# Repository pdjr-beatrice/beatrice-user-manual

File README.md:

# beatrice-user-manual

This Docbook 5 project implements a user manual for the motor vessel "Beatrice of Hull".

The src/ directory contains the XML source in Docbook 5 "book" format.

The pub/ directory contains renderings of the user manual in various formats. The latest PDF rendering is available
<a href="pub/pdf/beatrice.pdf" download="beatrice">here</a>.

The status of this work is DRAFT.

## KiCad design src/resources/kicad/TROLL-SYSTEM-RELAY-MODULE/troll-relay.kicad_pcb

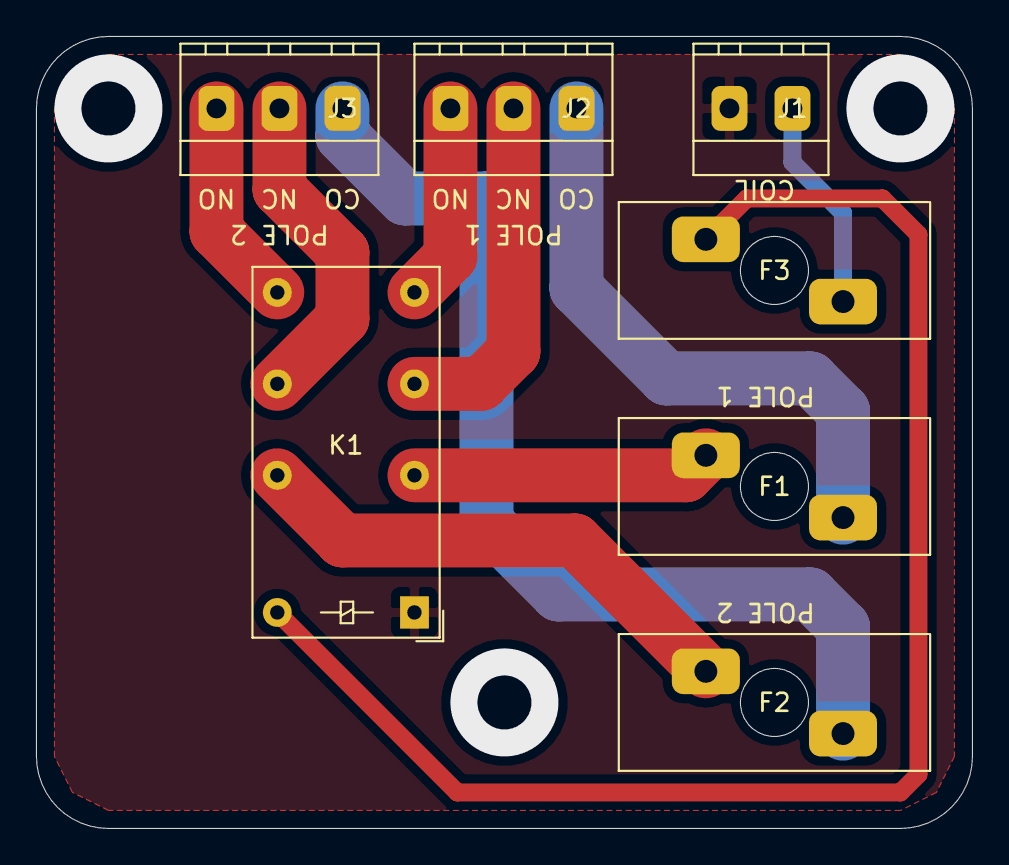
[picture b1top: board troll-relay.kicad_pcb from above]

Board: 2 copper layers, 52.0 x 44.0 mm, 7 parts (0 on the bottom side), 11 nets.

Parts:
F1, F2, F3: Fuse; LITTLEFUSE_153008
J1: Screw_Terminal_01x02; PHOENIX_MKDS_3.5MM_2-POLE_#1751248
J2, J3: Screw_Terminal_01x03; PHOENIX_MKDS_3.5MM_3-POLE_#1751251
K1: FINDER-30.22; Relay_DPDT_Finder_30.22

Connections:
unnamed: F1.1, K1.11
unnamed: F1.2, J2.1
unnamed: F2.1, K1.21
unnamed: F2.2, J3.1
unnamed: F3.1, K1.A2
unnamed: F3.2, J1.1
unnamed: J1.2, K1.A1
unnamed: J2.2, K1.12
unnamed: J2.3, K1.14
unnamed: J3.2, K1.22
unnamed: J3.3, K1.24

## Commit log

2018-04-27 Create LICENSE
2019-04-12 Added description of raw water deckwash facility
2019-04-28 Many small tidy ups
2019-04-28 Refactor
2019-04-28 Tidy
2019-04-28 New draft pdf
2019-04-28 Published rtf draft
2019-04-28 Refactor resource directories
2019-04-28 Resize logos
2019-04-28 New render
2019-04-29 Re-size icons
2019-04-30 Control panel revision
2019-04-30 Minor updates
2019-05-02 New section
2019-05-03 New section data-networks
2019-05-03 Minor edit
2019-05-04 Minor edits
2019-05-05 Removed infrastructure narrative
2019-05-05 More
2019-05-07 Cover image
2019-05-08 Panels
2019-05-09 DocBook format changes
2019-05-19 Hot water loop
2019-06-28 A strange load of changes
2019-07-01 Added solar charge system
2020-01-05 Troll valve plus minor mods
2020-01-05 Mods
2020-01-05 Revised troll
2020-01-05 Added troll panel cutting files
2020-01-08 Tidy up
2020-01-14 New kicad project
2020-02-03 Revised wiring
2022-01-04 Tidying up
2024-02-05 Rhubarb
2025-01-08 Add section for presence detection and alarm
2026-01-09 Add helm panel lighting on-off feature.
2026-01-10 Reformat switch diagram
2026-01-11 Add wire colors / sizes
2026-01-13 Tweak
2026-02-25 Many tweaks
2026-03-03 Swap dimmer polarity
